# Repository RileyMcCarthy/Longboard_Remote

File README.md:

"# Longboard_Remote" 
"# Longboard_Remote"

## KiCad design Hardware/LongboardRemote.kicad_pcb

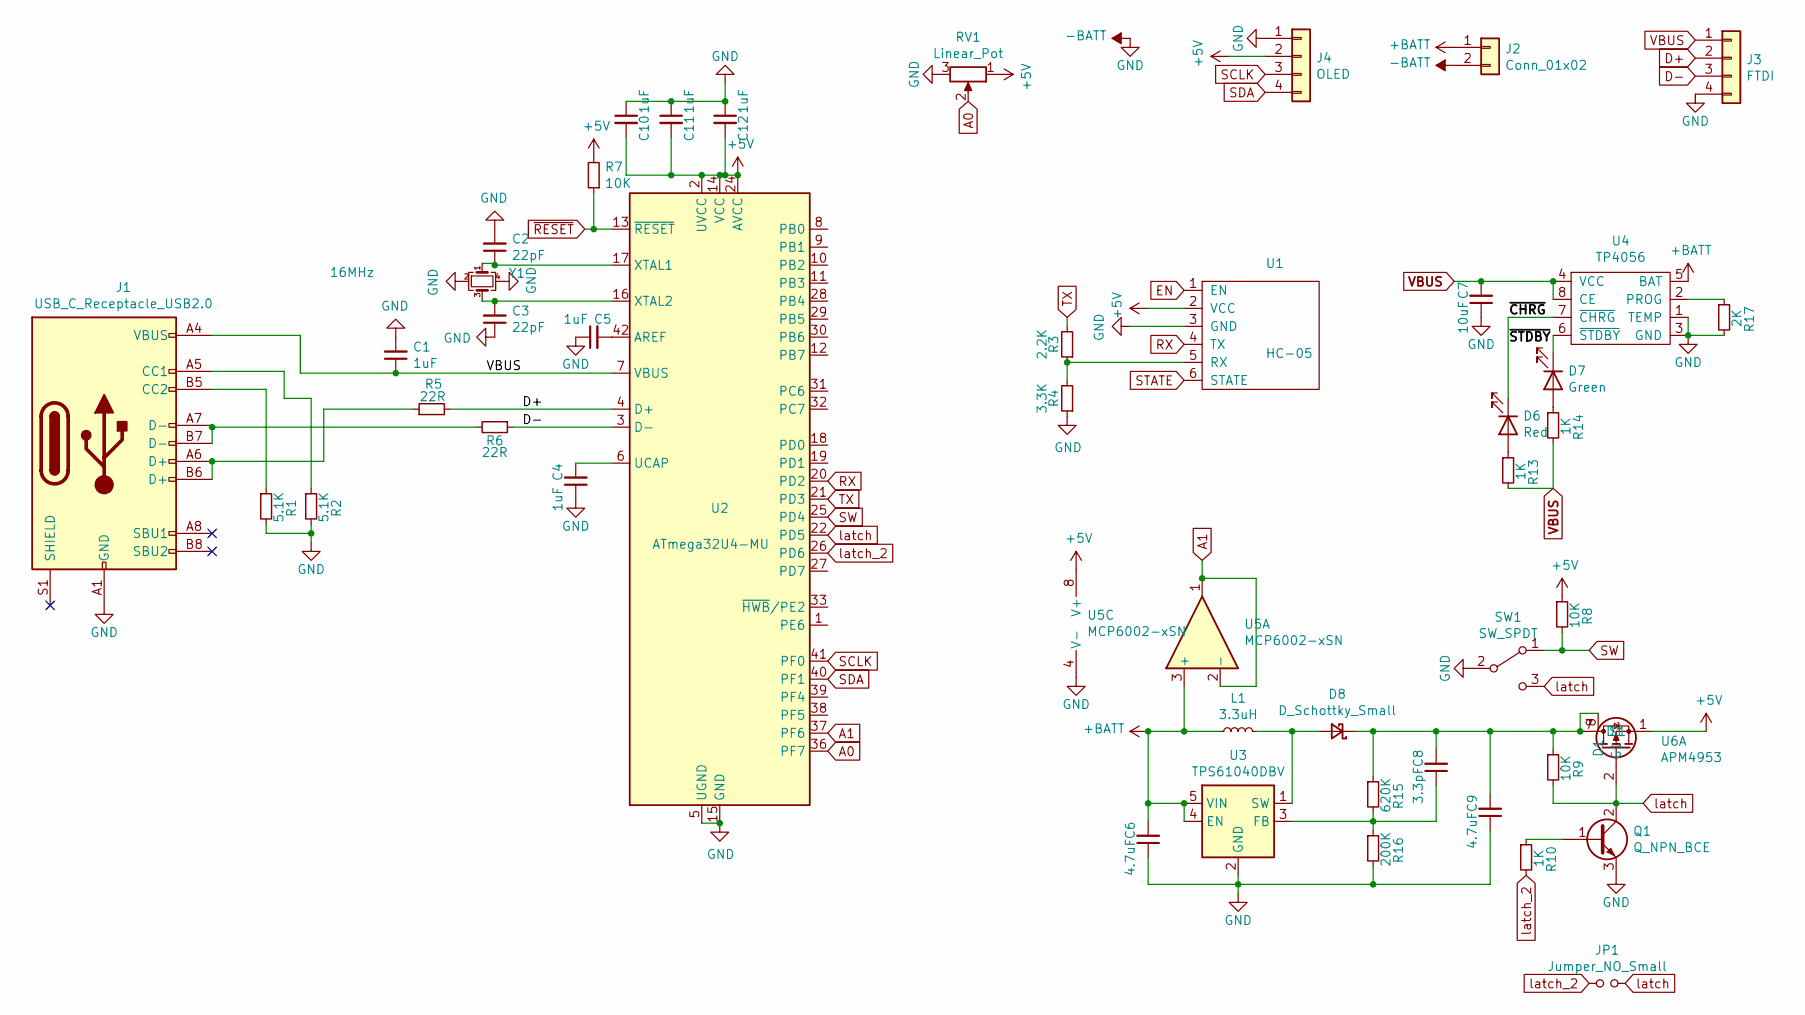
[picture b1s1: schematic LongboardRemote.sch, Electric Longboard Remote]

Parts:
C1, C4, C5, C10, C11, C12: 1uF; C_0603_1608Metric; LCSC C15849
C2, C3: 22pF; C_0603_1608Metric; LCSC C1653
C6, C9: 4.7uF; C_0603_1608Metric; LCSC C19666
C7: 10uF; C_0603_1608Metric; LCSC C19702
C8: 3.3pF; C_0402_1005Metric; LCSC C1565
D6: Red; LED_0603_1608Metric; LCSC C2286
D7: Green; LED_0603_1608Metric; LCSC C72043
D8: D_Schottky_Small; D_SOD-123; LCSC C8598
J1: USB_C_Receptacle_USB2.0; USB_C_Receptacle_Palconn_UTC16-G; LCSC C165948
J2: Conn_01x02; PinHeader_1x02_P2.54mm_Vertical
J3: FTDI; PinHeader_1x04_P2.54mm_Vertical
J4: OLED
JP1: Jumper_NO_Small; SolderJumper-2_P1.3mm_Open_Pad1.0x1.5mm
L1: 3.3uH; L_0805_2012Metric; LCSC C51725
Q1: Q_NPN_BCE; SOT-23; LCSC C2146
R1, R2: 5.1K; R_0603_1608Metric; LCSC C23186
R3: 2.2K; R_0603_1608Metric; LCSC C4190
R4: 3.3K; R_0603_1608Metric; LCSC C22978
R5, R6: 22R; R_0603_1608Metric; LCSC C23345
R7, R8: 10K; R_0603_1608Metric; LCSC C25804
R9: 10K; R_0603_1608Metric; LCSC C25803
R10: 1K; R_0603_1608Metric; LCSC C25803
R13, R14: 1K; R_0603_1608Metric; LCSC C21190
R15: 620K; R_0603_1608Metric; LCSC C23219
R16: 200K; R_0603_1608Metric; LCSC C25811
R17: 2K; R_0603_1608Metric; LCSC C22975
RV1: Linear_Pot; SlidePot
SW1: SW_SPDT; DM1-135C-1; LCSC C466015
U1: HC-05
U2: ATmega32U4-MU; TQFP-44-1EP_10x10mm_P0.8mm_EP4.5x4.5mm; LCSC C44854
U3: TPS61040DBV; SOT-23-5; LCSC C7722
U4: TP4056; SOP-8_3.9x4.9mm_P1.27mm; LCSC C16581
U5: MCP6002-xSN; SOIC-8_3.9x4.9mm_P1.27mm; LCSC C7377
U6: APM4953; SOP-8_3.9x4.9mm_P1.27mm; LCSC C20897
Y1: 16MHz; Crystal_SMD_3225-4Pin_3.2x2.5mm; LCSC C13738

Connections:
+5V: C10.2, C11.2, C12.2, J4.2, R7.2, R8.1, RV1.1, U1.2 (VCC), U2.2 (UVCC), U2.14 (VCC), U2.24 (AVCC), U2.34 (VCC), U2.44 (AVCC), U5.8 (V+), U6.1 (S1)
+BATT: C6.2, J2.1, L1.1, U3.4 (EN), U3.5 (VIN), U4.5 (BAT), U5.3 (+)
-BATT: C1.2, C2.2, C3.1, C4.1, C5.1, C6.1, C7.1, C9.1, C10.1, C11.1, C12.1, J1.A1 (GND), J1.A12 (GND), J1.B1 (GND), J1.B12 (GND), J2.2, J3.4, J4.1, Q1.3 (E), R1.2, R2.2, R4.1, R16.2, R17.2, RV1.3, SW1.2 (B), U1.3 (GND), U2.5 (UGND), U2.15 (GND), U2.23 (GND), U2.35 (GND), U2.43 (GND), U2.45 (GND), U3.2 (GND), U4.1 (TEMP), U4.3 (GND), U5.4 (V-), Y1.2, Y1.4
/~CHRG: D6.1 (K), U4.7 (~CHRG)
A0: RV1.2, U2.36 (PF7)
A1: U2.37 (PF6), U5.1, U5.2 (-)
D+: J3.2, R5.2, U2.4 (D+)
D-: J3.3, R6.1, U2.3 (D-)
EN: U1.1 (EN)
unnamed: C2.1, U2.17 (XTAL1), Y1.1
unnamed: C3.2, U2.16 (XTAL2), Y1.3
unnamed: C4.2, U2.6 (UCAP)
unnamed: C5.2, U2.42 (AREF)
unnamed: C8.1, R15.2, R16.1, U3.3 (FB)
unnamed: C8.2, C9.2, D8.1 (K), R9.1, R15.1, U6.7 (D1), U6.8 (D1)
unnamed: D6.2 (A), R13.1
unnamed: D7.1 (K), U4.6 (~STDBY)
unnamed: D7.2 (A), R14.1
unnamed: D8.2 (A), L1.2, U3.1 (SW)
unnamed: J1.A5 (CC1), R2.1
unnamed: J1.A6 (D+), J1.B6 (D+), R5.1
unnamed: J1.A7 (D-), J1.B7 (D-), R6.2
unnamed: J1.B5 (CC2), R1.1
unnamed: Q1.1 (B), R10.1
unnamed: R3.1, R4.2, U1.5 (RX)
unnamed: R17.1, U4.2 (PROG)
RX: U1.4 (TX), U2.20 (PD2)
SCLK: J4.3, U2.41 (PF0)
SDA: J4.4, U2.40 (PF1)
STATE: U1.6 (STATE)
SW: R8.2, SW1.1 (A), U2.25 (PD4)
TX: R3.2, U2.21 (PD3)
VBUS: C1.1, C7.2, J1.A4 (VBUS), J1.A9 (VBUS), J1.B4 (VBUS), J1.B9 (VBUS), J3.1, R13.2, R14.2, U2.7 (VBUS), U4.4 (VCC), U4.8 (CE)
latch: JP1.2, Q1.2 (C), R9.2, SW1.3 (C), U2.22 (PD5), U6.2 (G1)
latch_2: JP1.1, R10.2, U2.26 (PD6)
~RESET: R7.1, U2.13 (~RESET)

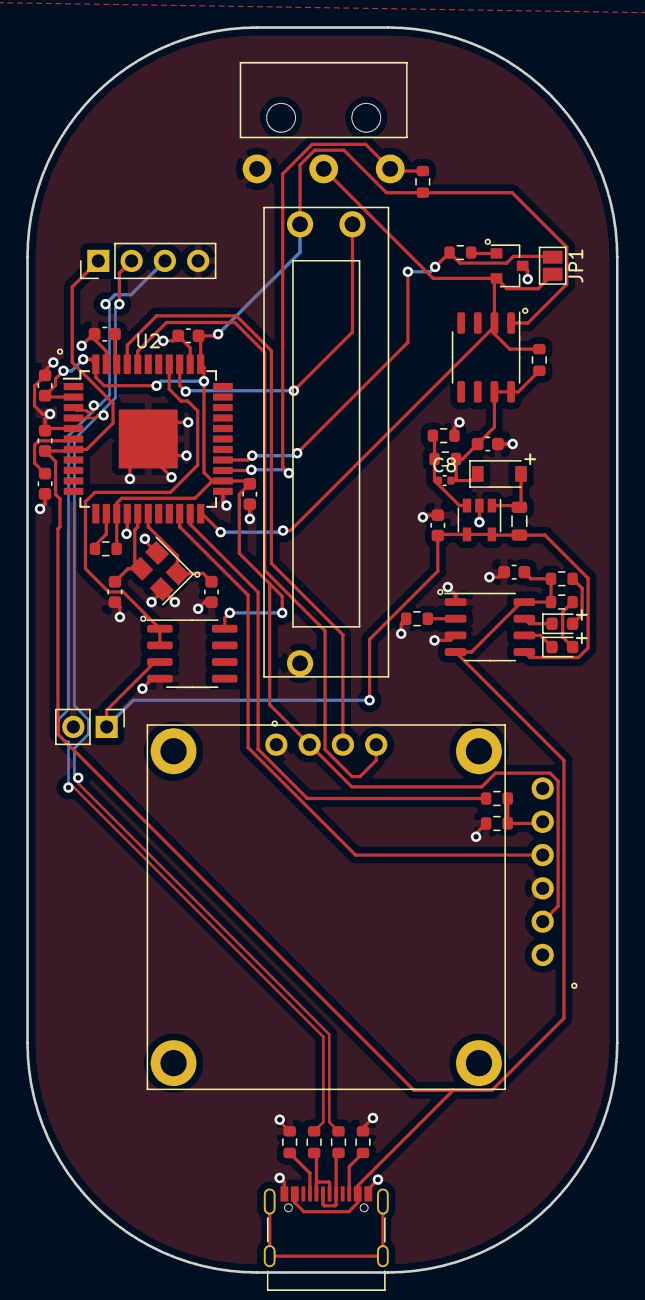
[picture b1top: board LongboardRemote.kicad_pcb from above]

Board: 2 copper layers, 45.0 x 95.0 mm, 46 parts (1 on the bottom side), 34 nets.
